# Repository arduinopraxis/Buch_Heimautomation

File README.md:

# Buch_Heimautomation
Maker Book "Heimautomation mit Arduino, ESP8266 und Raspberry Pi" (German)

see
https://www.555circuitslab.com/buecher/

Das Buch ist im Buchhandel, beim Verlag oder Amazon verfügbar

https://www.mitp.de/IT-WEB/Elektronik-Maker/Heimautomation-mit-Arduino-ESP8266-und-Raspberry-Pi.html

http://www.amazon.de/exec/obidos/ASIN/3958456715/webmeisterch-21

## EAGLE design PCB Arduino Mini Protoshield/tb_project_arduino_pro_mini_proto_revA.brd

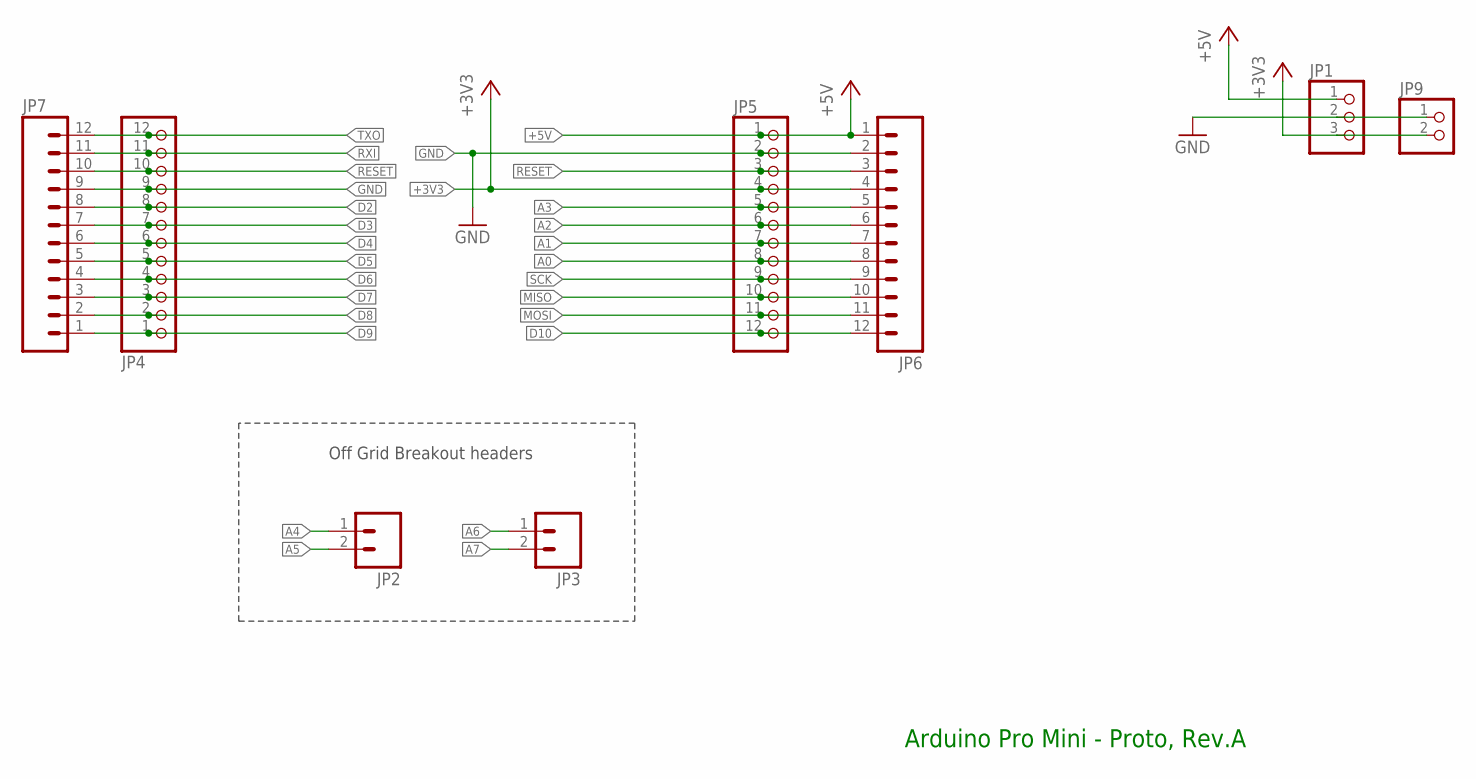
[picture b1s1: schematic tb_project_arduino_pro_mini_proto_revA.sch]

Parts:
JP1: PINHD-1X3; 1X03
JP2, JP3: M02PTH; 1X02
JP4, JP5: PINHD-1X12; 1X12
JP6, JP7: M12PTH; 1X12
JP9: PINHD-1X2; 1X02

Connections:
+3V3: JP1.3, JP5.4, JP6.4, JP9.2
+5V: JP1.1, JP5.1, JP6.1
A0: JP5.8, JP6.8
A1: JP5.7, JP6.7
A2: JP5.6, JP6.6
A3: JP5.5, JP6.5
A4: JP2.1
A5: JP2.2
A6: JP3.1
A7: JP3.2
D2: JP4.8, JP7.8
D3: JP4.7, JP7.7
D4: JP4.6, JP7.6
D5: JP4.5, JP7.5
D6: JP4.4, JP7.4
D7: JP4.3, JP7.3
D8: JP4.2, JP7.2
D9: JP4.1, JP7.1
D10: JP5.12, JP6.12
GND: JP1.2, JP4.9, JP5.2, JP6.2, JP7.9, JP9.1
MISO: JP5.10, JP6.10
MOSI: JP5.11, JP6.11
RESET: JP4.10, JP5.3, JP6.3, JP7.10
RXI: JP4.11, JP7.11
SCK: JP5.9, JP6.9
TXO: JP4.12, JP7.12

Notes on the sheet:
Off Grid Breakout headers
Arduino Pro Mini - Proto, Rev.A

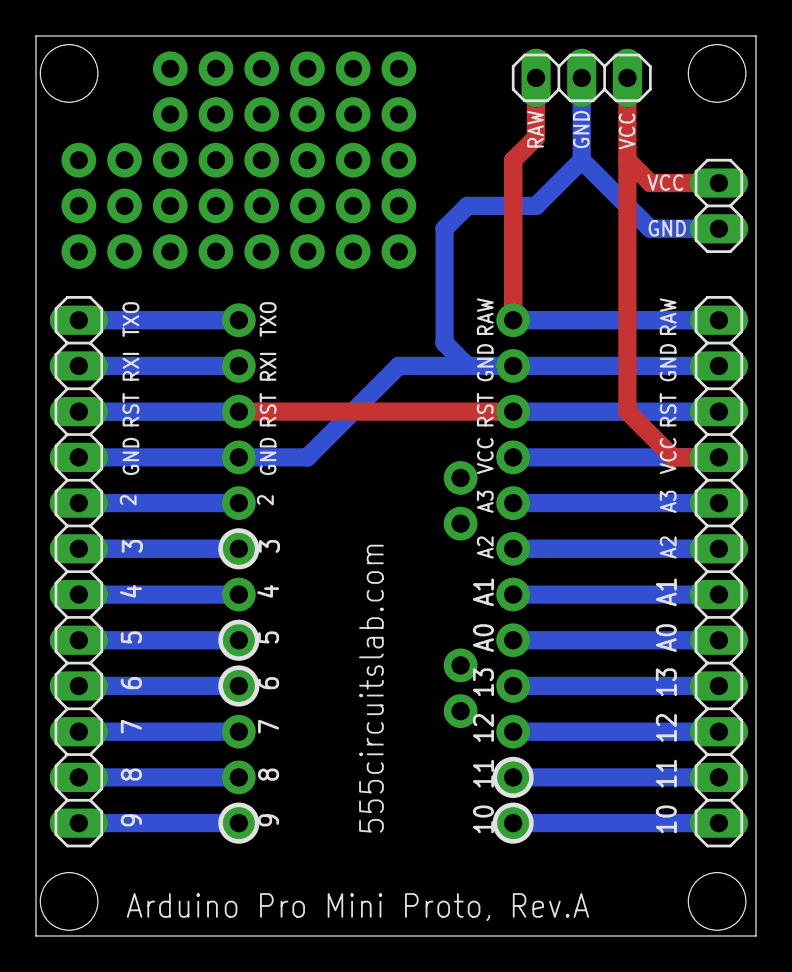
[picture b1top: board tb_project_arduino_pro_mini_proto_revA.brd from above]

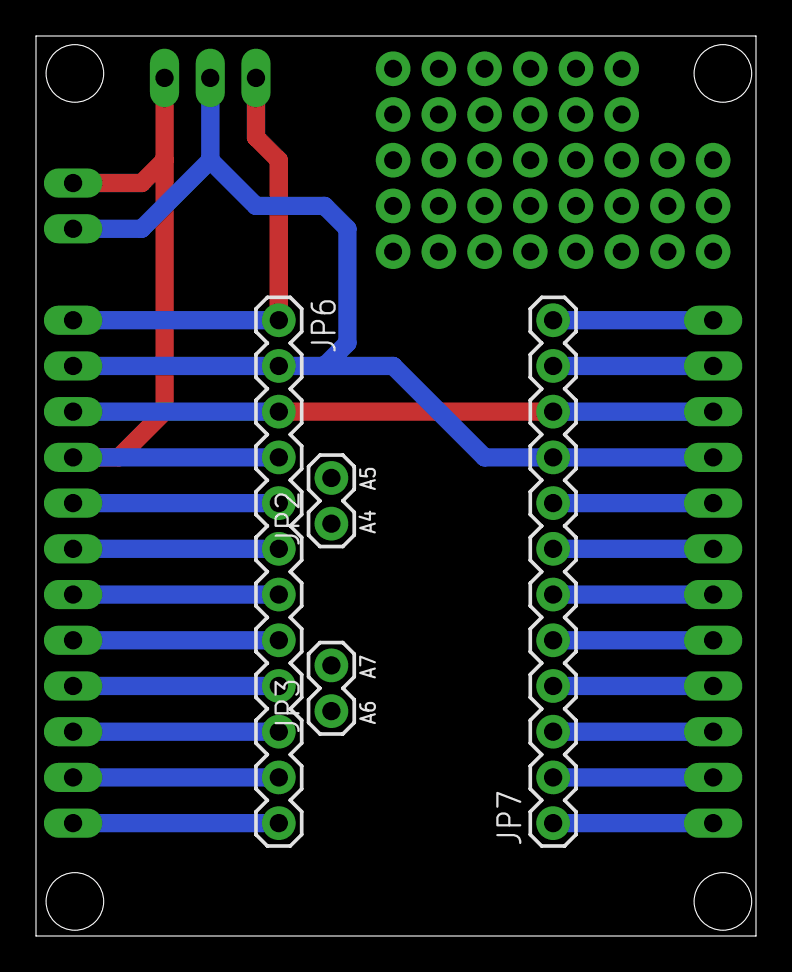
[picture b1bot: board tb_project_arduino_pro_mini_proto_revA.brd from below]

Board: 2 copper layers, 40.0 x 50.0 mm, 8 parts (4 on the bottom side), 22 nets.

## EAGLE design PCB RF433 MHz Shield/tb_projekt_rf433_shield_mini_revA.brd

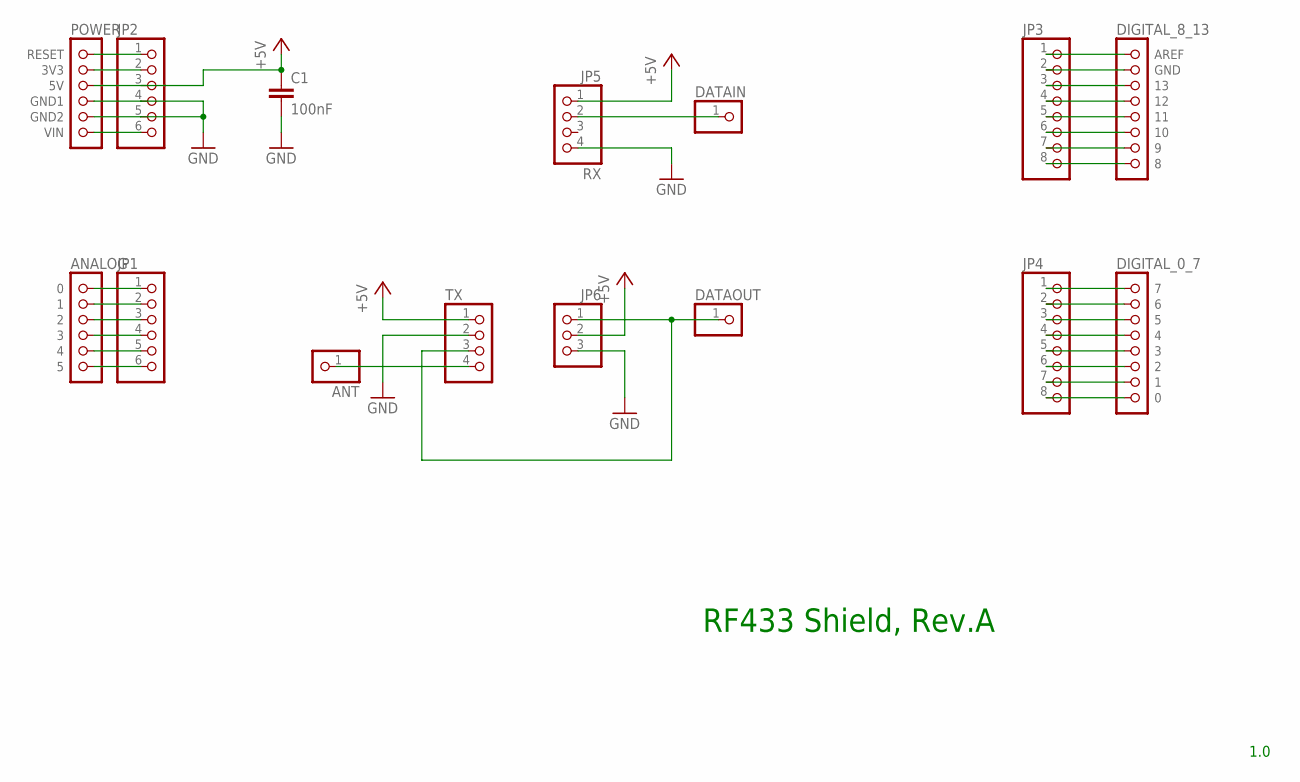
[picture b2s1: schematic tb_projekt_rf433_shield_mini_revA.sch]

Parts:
ANT: PINHD-1X1; 1X01
C1: 100nF; C025-024X044
DATAIN: PINHD-1X1; 1X01
DATAOUT: PINHD-1X1; 1X01
JP1, JP2: PINHD-1X6; 1X06
JP3, JP4: PINHD-1X8; 1X08
JP5: RX; 1X04
JP6: PINHD-1X3; 1X03
TX: PINHD-1X4; 1X04
U$1: POWER; 1X06
U$2: ANALOG; 1X06
U$3: DIGITAL_0_7; 1X08
U$4: DIGITAL_8_13; 1X08

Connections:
+5V: C1.1, JP2.3, JP5.1, JP6.2, TX.1, U$1.3 (5V)
GND: C1.2, JP2.4, JP2.5, JP5.4, JP6.3, TX.2, U$1.4 (GND1), U$1.5 (GND2)
unnamed: JP1.1, U$2.1 (0)
unnamed: JP1.2, U$2.2 (1)
unnamed: JP2.2, U$1.2 (3V3)
unnamed: DATAIN.1, JP5.2
unnamed: ANT.1, TX.4
unnamed: JP4.5, U$3.5 (3)
unnamed: JP1.3, U$2.3 (2)
unnamed: JP1.4, U$2.4 (3)
unnamed: JP1.5, U$2.5 (4)
unnamed: JP1.6, U$2.6 (5)
unnamed: JP2.6, U$1.6 (VIN)
unnamed: JP2.1, U$1.1 (RESET)
unnamed: JP3.1, U$4.1 (AREF)
unnamed: JP3.2, U$4.2 (GND)
unnamed: JP3.3, U$4.3 (13)
unnamed: JP3.4, U$4.4 (12)
unnamed: JP3.5, U$4.5 (11)
unnamed: JP3.7, U$4.7 (9)
unnamed: JP3.8, U$4.8
unnamed: JP4.6, U$3.6 (2)
unnamed: JP4.7, U$3.7 (1)
unnamed: JP4.8, U$3.8 (0)
unnamed: JP4.4, U$3.4
unnamed: JP4.3, U$3.3 (5)
unnamed: JP4.2, U$3.2 (6)
unnamed: JP4.1, U$3.1 (7)
RFDATA: DATAOUT.1, JP6.1, TX.3
SS: JP3.6, U$4.6 (10)

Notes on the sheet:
RF433 Shield, Rev.A
1.0

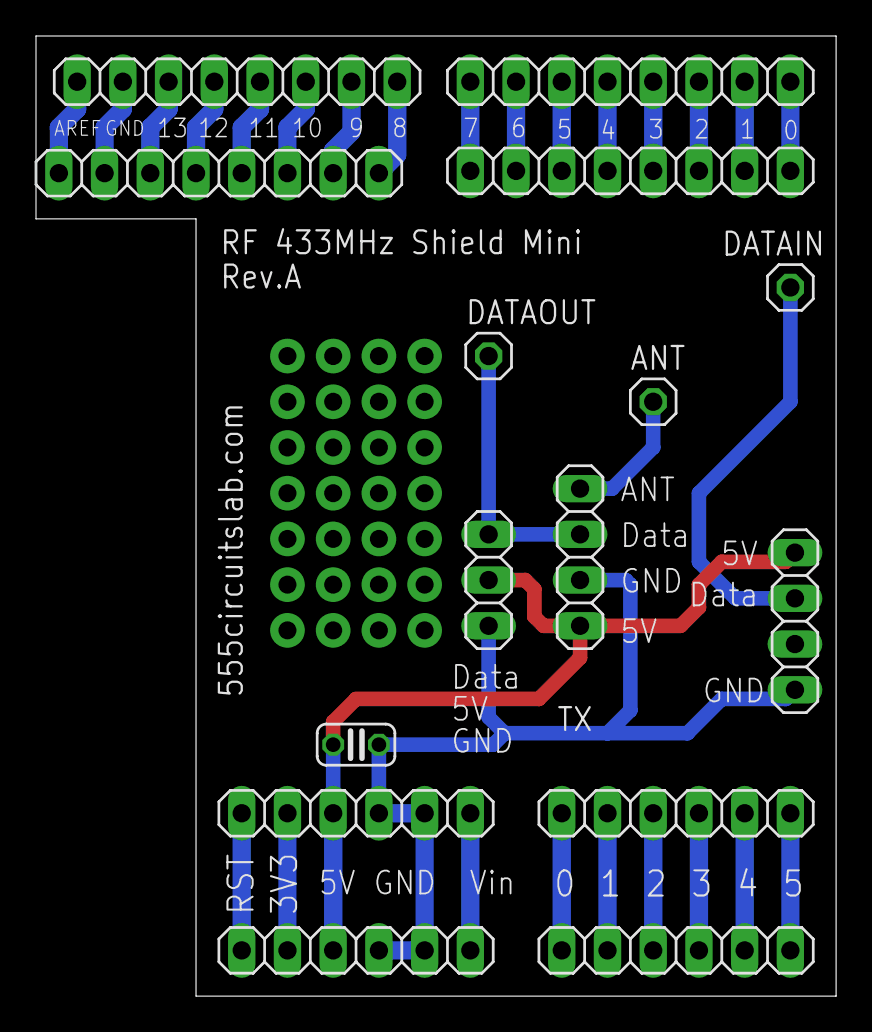
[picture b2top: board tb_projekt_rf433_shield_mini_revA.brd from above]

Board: 2 copper layers, 44.5 x 53.3 mm, 15 parts (0 on the bottom side), 30 nets.

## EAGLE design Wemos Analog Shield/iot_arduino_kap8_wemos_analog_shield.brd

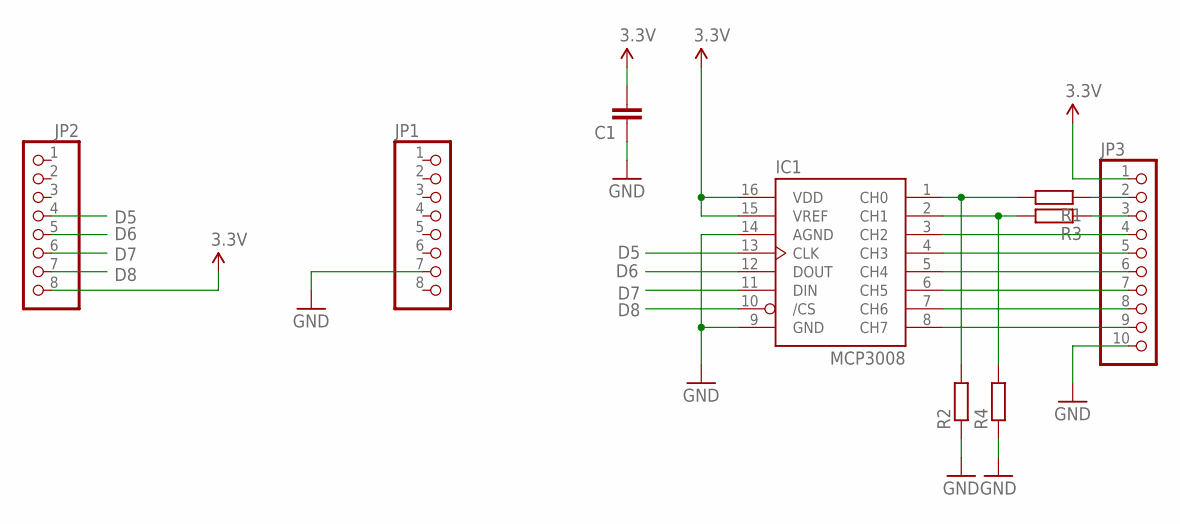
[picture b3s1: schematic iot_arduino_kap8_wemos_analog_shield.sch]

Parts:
C1: C-EUC0805K; C0805K
IC1: MCP3008; DIL16
JP1, JP2: PINHD-1X8; 1X08
JP3: PINHD-1X10; 1X10
R1, R2, R3, R4: R-EU_M0805; M0805

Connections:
3.3V: C1.2, IC1.15 (VREF), IC1.16 (VDD), JP2.8, JP3.1
D5: IC1.13 (CLK), JP2.4
D6: IC1.12 (DOUT), JP2.5
D7: IC1.11 (DIN), JP2.6
D8: IC1.10 (/CS), JP2.7
GND: C1.1, IC1.9 (GND), IC1.14 (AGND), JP1.7, JP3.10, R2.1, R4.1
unnamed: JP3.2, R1.1
unnamed: IC1.1 (CH0), R1.2, R2.2
unnamed: IC1.2 (CH1), R3.2, R4.2
unnamed: JP3.3, R3.1
unnamed: IC1.3 (CH2), JP3.4
unnamed: IC1.4 (CH3), JP3.5
unnamed: IC1.5 (CH4), JP3.6
unnamed: IC1.6 (CH5), JP3.7
unnamed: IC1.7 (CH6), JP3.8
unnamed: IC1.8 (CH7), JP3.9

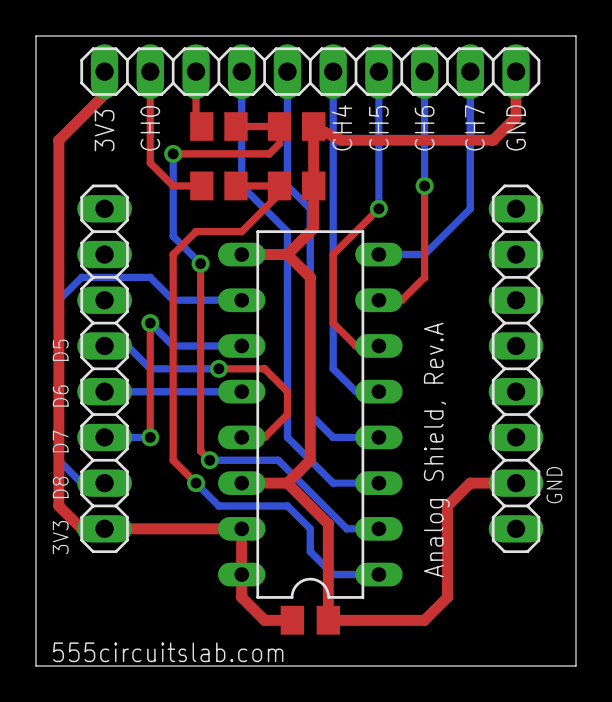
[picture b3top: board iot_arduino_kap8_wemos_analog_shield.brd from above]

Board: 2 copper layers, 30.0 x 35.0 mm, 9 parts (0 on the bottom side), 16 nets.

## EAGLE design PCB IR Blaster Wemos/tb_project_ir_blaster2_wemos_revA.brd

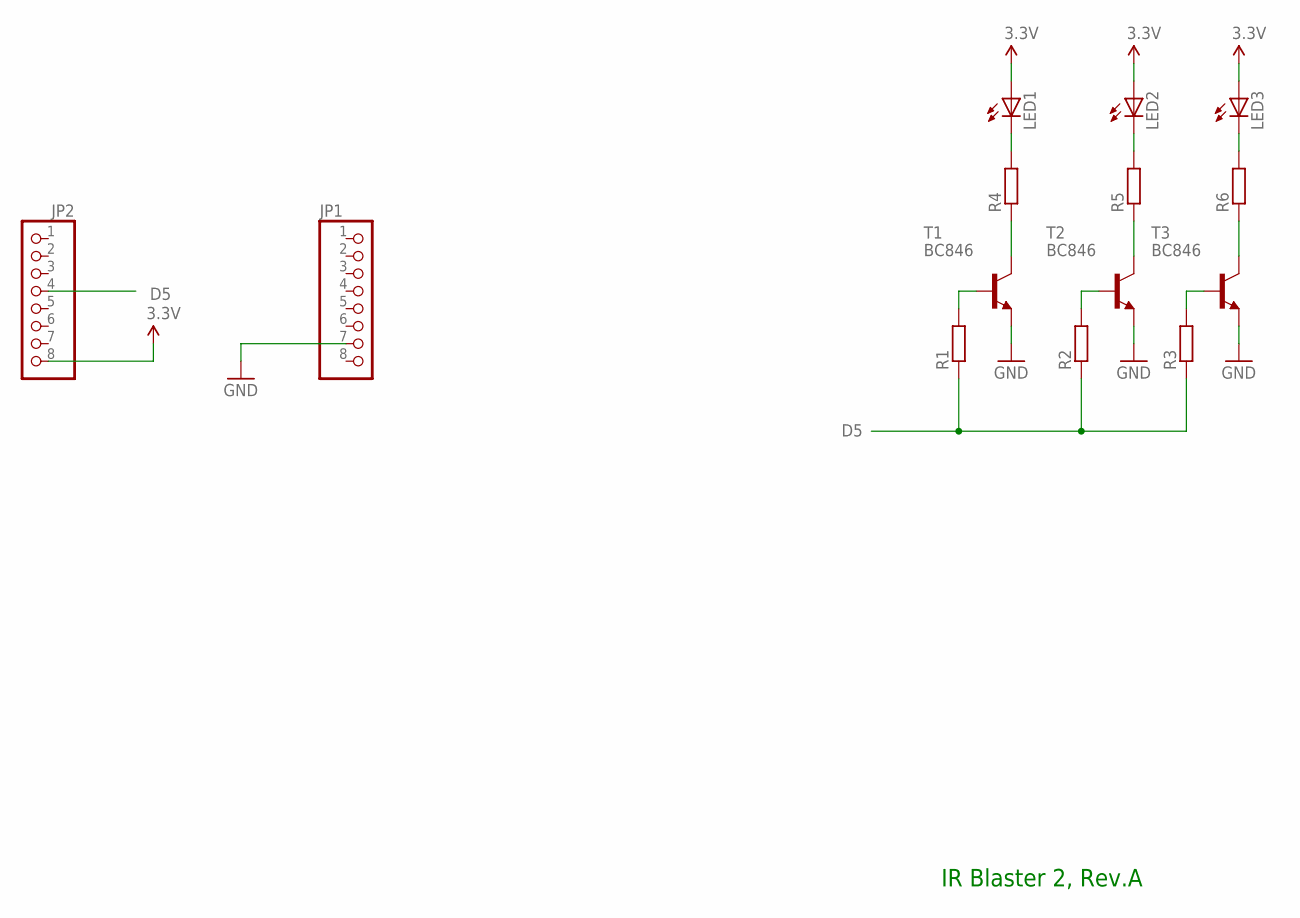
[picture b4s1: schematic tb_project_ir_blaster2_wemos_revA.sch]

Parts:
JP1, JP2: PINHD-1X8; 1X08
LED1, LED2, LED3: LED5MM
R1, R2, R3, R4, R5, R6: R-EU_R1206; R1206
T1, T2, T3: BC846; SOT23

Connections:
3.3V: JP2.8, LED1.A, LED2.A, LED3.A
D5: JP2.4, R1.1, R2.1, R3.1
GND: JP1.7, T1.2 (E), T2.2 (E), T3.2 (E)
unnamed: LED1.K (C), R4.2
unnamed: LED2.K (C), R5.2
unnamed: LED3.K (C), R6.2
unnamed: R4.1, T1.3 (C)
unnamed: R5.1, T2.3 (C)
unnamed: R6.1, T3.3 (C)
unnamed: R1.2, T1.1 (B)
unnamed: R2.2, T2.1 (B)
unnamed: R3.2, T3.1 (B)

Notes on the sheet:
IR Blaster 2, Rev.A

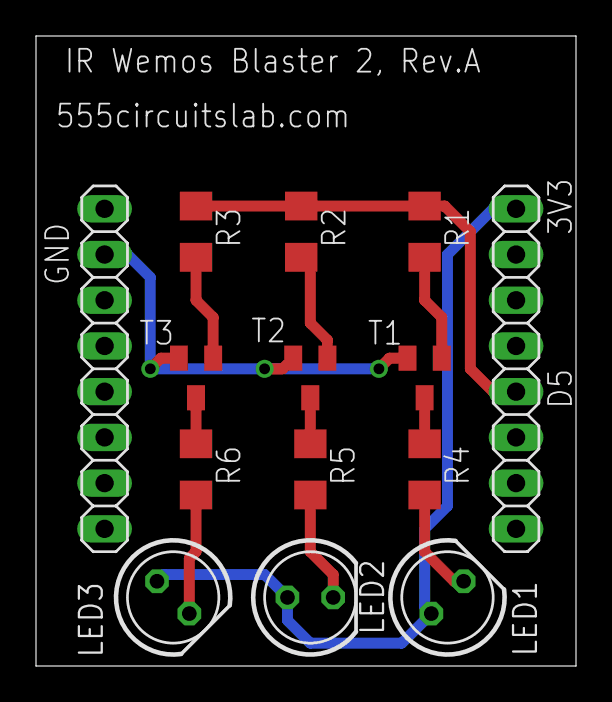
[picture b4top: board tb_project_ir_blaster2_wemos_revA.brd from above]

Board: 2 copper layers, 30.0 x 35.0 mm, 14 parts (0 on the bottom side), 12 nets.

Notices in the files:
parts and their libraries:
freetronics-original: Licensing: CC v3.0 Share-Alike You are welcome to use this library for commercial purposes.
